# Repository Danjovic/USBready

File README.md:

# USBready
USB breadboard ready development board

Uses [USBaspLoader](https://www.obdev.at/products/vusb/usbasploader.html) as a bootloader. 

Precompiled .hex files available on 
[repository ](/Firmware/Bootloader/USBaspLoader.2012-12-08/hexfiles/)

PCB shared at [OSHPark](https://oshpark.com/shared_projects/ElsYFBDc)

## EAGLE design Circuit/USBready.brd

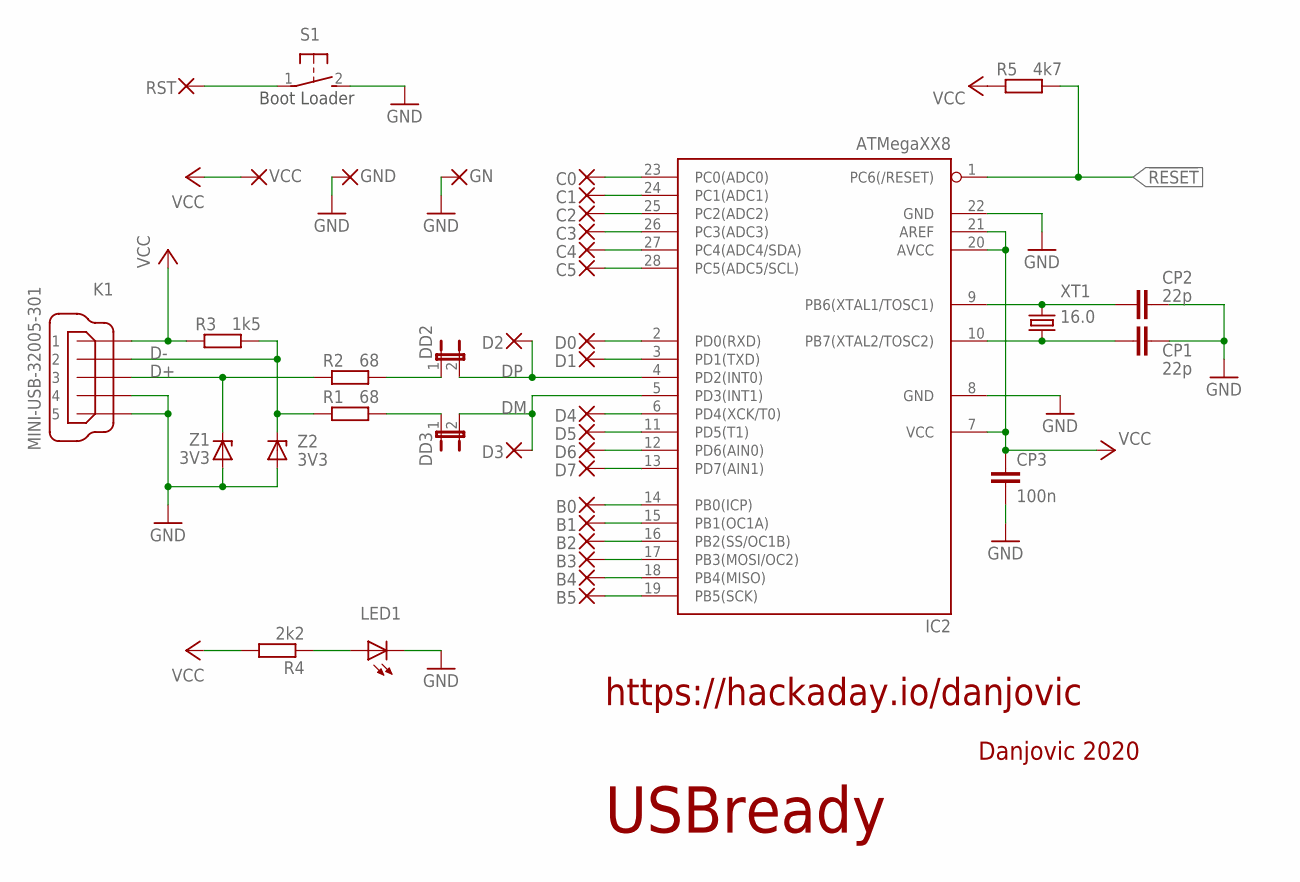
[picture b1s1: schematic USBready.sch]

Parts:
B0, B1, B2, B3, B4, B5: WIREPAD1,6/0,9; 1,6/0,9
C0, C1, C2, C3, C4, C5: WIREPAD1,6/0,9; 1,6/0,9
CP1, CP2: 22p; C0805
CP3: 100n; C0805
D0, D1, D2, D3, D4, D5, D6, D7: WIREPAD1,6/0,9; 1,6/0,9
DD2, DD3: JP1E; JP1
GN: WIREPAD1,6/0,9; 1,6/0,9
GND: WIREPAD1,6/0,9; 1,6/0,9
IC2: ATMegaXX8; DIL28-3
K1: MINI-USB-32005-301; 32005-301
LED1: LEDSML1206; SML1206
R1, R2: 68; M0805
R3: 1k5; R0805
R4: 2k2; R0805
R5: 4k7; M0805
RST: WIREPAD1,6/0,9; 1,6/0,9
S1: 31-XX; B3F-31XX
VCC: WIREPAD1,6/0,9; 1,6/0,9
XT1: 16.0; HC49/S
Z1, Z2: 3V3; SOD80C

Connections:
!RESET: IC2.1 (PC6(/RESET)), R5.2, RST.1, S1.1
AN2: C2.1, IC2.25 (PC2(ADC2))
AN3: C3.1, IC2.26 (PC3(ADC3))
D+: K1.3, R2.1, Z1.C
D-: K1.2, R1.1, R3.2, Z2.C
DM: D3.1, DD3.2, IC2.5 (PD3(INT1))
DP: D2.1, DD2.2, IC2.4 (PD2(INT0))
GND: CP1.2, CP2.2, CP3.2, GN.1, GND.1, IC2.8 (GND), IC2.22 (GND), K1.4, K1.5, LED1.C, S1.2 (S), Z1.A, Z2.A
unnamed: D0.1, IC2.2 (PD0(RXD))
unnamed: D4.1, IC2.6 (PD4(XCK/T0))
unnamed: C1.1, IC2.24 (PC1(ADC1))
unnamed: C0.1, IC2.23 (PC0(ADC0))
unnamed: C4.1, IC2.27 (PC4(ADC4/SDA))
unnamed: C5.1, IC2.28 (PC5(ADC5/SCL))
unnamed: D1.1, IC2.3 (PD1(TXD))
unnamed: D5.1, IC2.11 (PD5(T1))
unnamed: D6.1, IC2.12 (PD6(AIN0))
unnamed: D7.1, IC2.13 (PD7(AIN1))
unnamed: LED1.A, R4.1
unnamed: B0.1, IC2.14 (PB0(ICP))
unnamed: B2.1, IC2.16 (PB2(SS/OC1B))
unnamed: B1.1, IC2.15 (PB1(OC1A))
unnamed: B5.1, IC2.19 (PB5(SCK))
unnamed: B4.1, IC2.18 (PB4(MISO))
unnamed: B3.1, IC2.17 (PB3(MOSI/OC2))
unnamed: DD2.1, R2.2
unnamed: DD3.1, R1.2
VCC: CP3.1, IC2.7 (VCC), IC2.20 (AVCC), IC2.21 (AREF), K1.1, R3.1, R4.2, R5.1, VCC.1
X1: CP2.1, IC2.9 (PB6(XTAL1/TOSC1)), XT1.2
X2: CP1.1, IC2.10 (PB7(XTAL2/TOSC2)), XT1.1

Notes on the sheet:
Boot Loader
Danjovic 2020
USBready
https://hackaday.io/danjovic

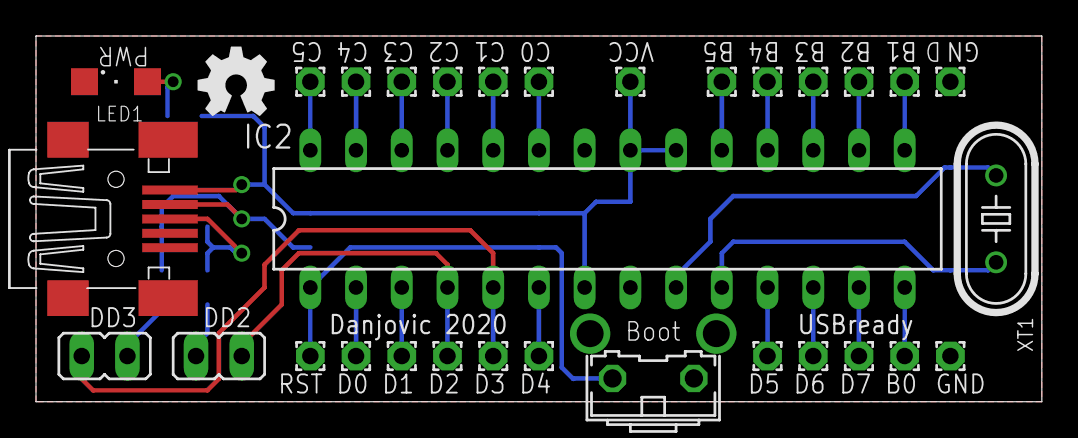
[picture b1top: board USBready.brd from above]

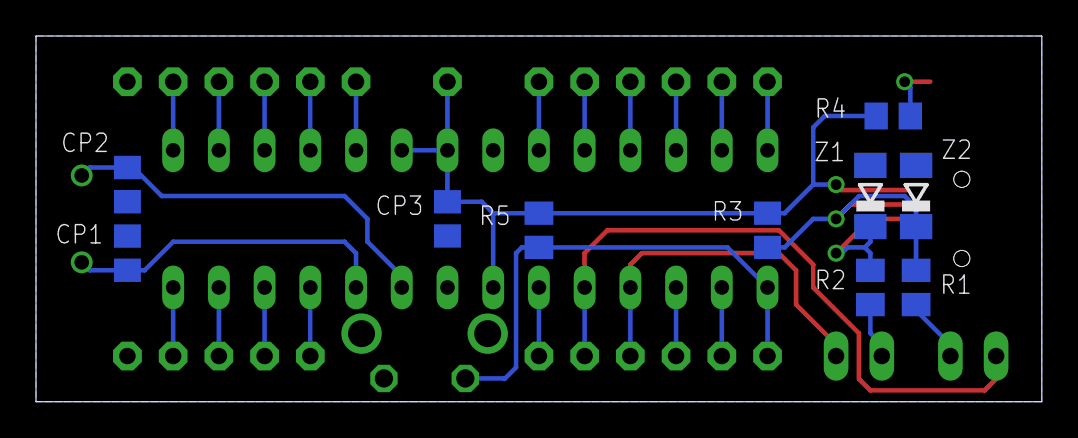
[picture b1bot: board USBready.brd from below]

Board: 2 copper layers, 55.9 x 20.3 mm, 41 parts (10 on the bottom side), 30 nets.
